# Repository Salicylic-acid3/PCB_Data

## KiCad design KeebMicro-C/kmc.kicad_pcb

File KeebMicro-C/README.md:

# KeebMicro-C

The KeebMicro-C is a Pro Micro compatible microcontroller board designed for DIY mechanical keyboards in Japan.
It is based on the same Atmel ATMega32U4 chip and can be programmed using Arduino IDE or keyboard-specific firmware such as TMK or QMK.
Conthrough, commonly used in Japan, eliminates the need for soldering.

## Links

- [fork root](https://github.com/staticintlucas/goldfish)

## Changes compared to Goldfish v2

- Conthrough support
- Reduced board outline
- Changed logo
- Added through-hole for external USB connector

## License

Released under the Creative Commons Attribution Share-Alike 4.0 License.
https://creativecommons.org/licenses/by-sa/4.0/

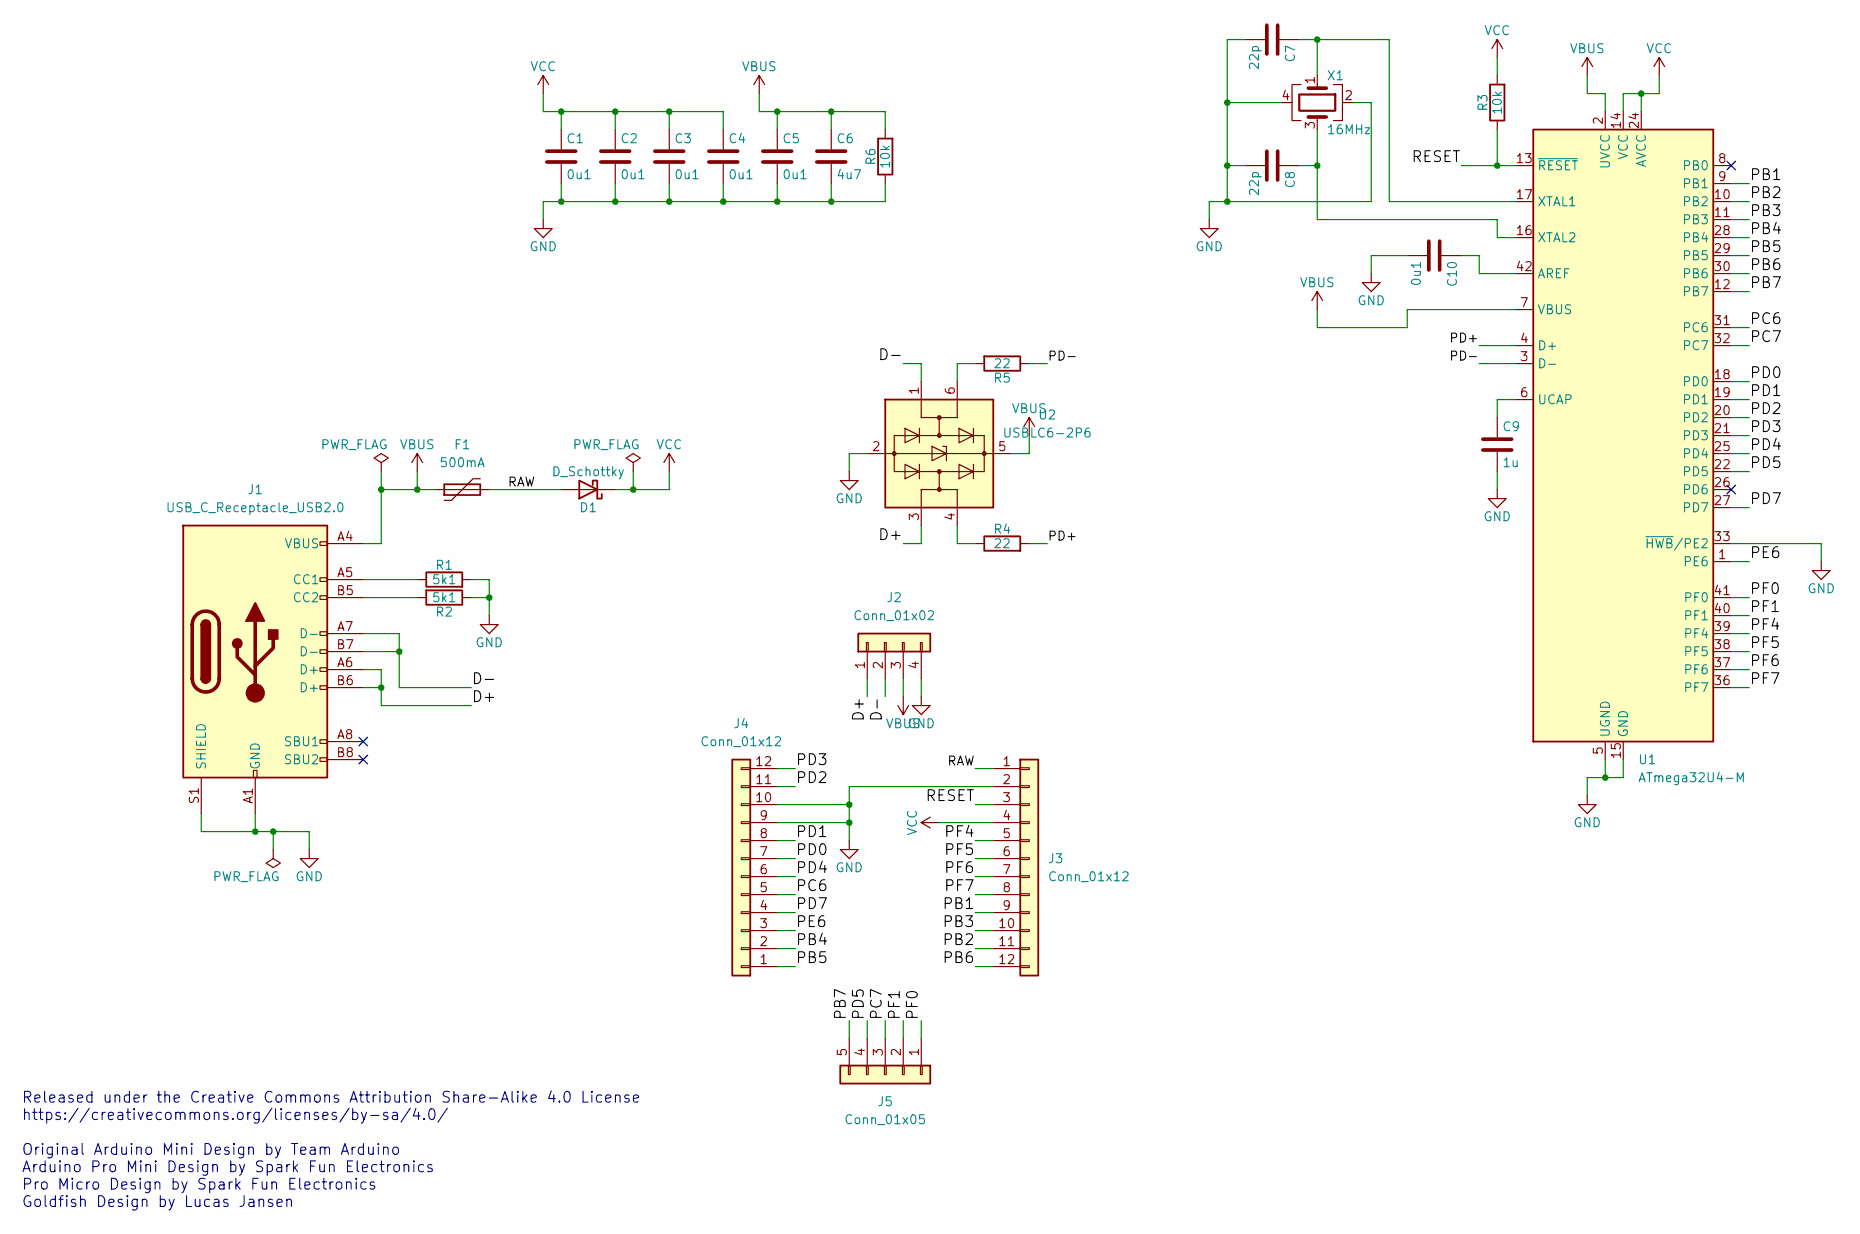
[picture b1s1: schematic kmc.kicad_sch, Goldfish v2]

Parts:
C1, C2, C3, C4, C5, C10: 0u1; C_0603_1608Metric
C6: 4u7; C_0603_1608Metric
C7, C8: 22p; C_0603_1608Metric
C9: 1u; C_0603_1608Metric
D1: D_Schottky; D_SOD-123F
F1: 500mA; Fuse_0805_2012Metric
J1: USB_C_Receptacle_USB2.0; Molex-216990_GCT-USB45xx_HRO-TYPE-C-31-M-13x
J2: Conn_01x02; Pins_USB
J3, J4: Conn_01x12; Pins_x12_Castellated
J5: Conn_01x05; Pins_x05_Castellated
R1, R2: 5k1; R_0603_1608Metric
R3, R6: 10k; R_0603_1608Metric
R4, R5: 22; R_0603_1608Metric
U1: ATmega32U4-M; QFN-44-1EP_7x7mm_P0.5mm_EP5.2x5.2mm
U2: USBLC6-2P6; SOT-666
X1: 16MHz; Crystal_SMD_SeikoEpson_FA238-4Pin_3.2x2.5mm

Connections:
/D+: J1.A6 (D+), J1.B6 (D+), J2.1, U2.3 (I/O2)
/D-: J1.A7 (D-), J1.B7 (D-), J2.2, U2.1 (I/O1)
/PB1: J3.9, U1.9 (PB1)
/PB2: J3.11, U1.10 (PB2)
/PB3: J3.10, U1.11 (PB3)
/PB4: J4.2, U1.28 (PB4)
/PB5: J4.1, U1.29 (PB5)
/PB6: J3.12, U1.30 (PB6)
/PB7: J5.5, U1.12 (PB7)
/PC6: J4.5, U1.31 (PC6)
/PC7: J5.3, U1.32 (PC7)
/PD0: J4.7, U1.18 (PD0)
/PD1: J4.8, U1.19 (PD1)
/PD2: J4.11, U1.20 (PD2)
/PD3: J4.12, U1.21 (PD3)
/PD4: J4.6, U1.25 (PD4)
/PD5: J5.4, U1.22 (PD5)
/PD7: J4.4, U1.27 (PD7)
/PD+: R4.2, U1.4 (D+)
/PD-: R5.1, U1.3 (D-)
/PE6: J4.3, U1.1 (PE6)
/PF0: J5.1, U1.41 (PF0)
/PF1: J5.2, U1.40 (PF1)
/PF4: J3.5, U1.39 (PF4)
/PF5: J3.6, U1.38 (PF5)
/PF6: J3.7, U1.37 (PF6)
/PF7: J3.8, U1.36 (PF7)
/RAW: D1.2 (A), F1.2, J3.1
/RESET: J3.3, R3.1, U1.13 (~RESET)
GND: C1.2, C2.2, C3.2, C4.2, C5.2, C6.2, C7.2, C8.2, C9.2, C10.2, J1.A1 (GND), J1.A12 (GND), J1.B1 (GND), J1.B12 (GND), J1.S1 (SHIELD), J2.4, J3.2, J4.9, J4.10, R1.2, R2.1, R6.1, U1.5 (UGND), U1.15 (GND), U1.23 (GND), U1.33 (~HWB/PE2), U1.35 (GND), U1.43 (GND), U1.45 (GND), U2.2 (GND), X1.2, X1.4
unnamed: J1.A5 (CC1), R1.1
unnamed: J1.B5 (CC2), R2.2
unnamed: R4.1, U2.4 (I/O2)
unnamed: R5.2, U2.6 (I/O1)
unnamed: C10.1, U1.42 (AREF)
unnamed: C9.1, U1.6 (UCAP)
unnamed: C7.1, U1.17 (XTAL1), X1.1
unnamed: C8.1, U1.16 (XTAL2), X1.3
VBUS: C5.1, C6.1, F1.1, J1.A4 (VBUS), J1.A9 (VBUS), J1.B4 (VBUS), J1.B9 (VBUS), J2.3, R6.2, U1.2 (UVCC), U1.7 (VBUS), U2.5 (VBUS)
VCC: C1.1, C2.1, C3.1, C4.1, D1.1 (K), J3.4, R3.2, U1.14 (VCC), U1.24 (AVCC), U1.34 (VCC), U1.44 (AVCC)

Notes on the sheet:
Released under the Creative Commons Attribution Share-Alike 4.0 License https://creativecommons.org/licenses/by-sa/4.0/ Original Arduino Mini Design by Team Arduino Arduino Pro Mini Design by Spark Fun Electronics Pro Micro Design by Spark Fun Electronics Goldfish Design by Lucas Jansen

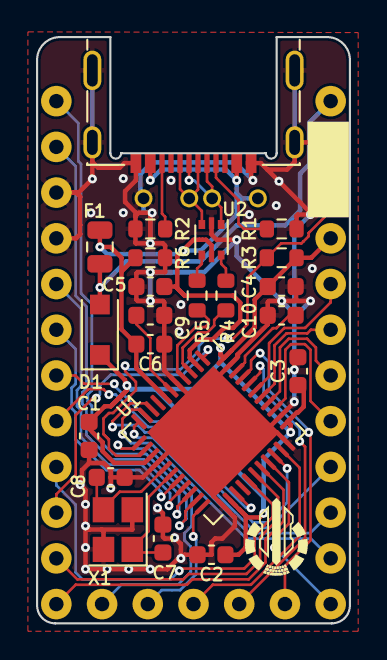
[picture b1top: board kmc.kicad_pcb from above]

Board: 2 copper layers, 17.4 x 32.6 mm, 26 parts (0 on the bottom side), 40 nets.

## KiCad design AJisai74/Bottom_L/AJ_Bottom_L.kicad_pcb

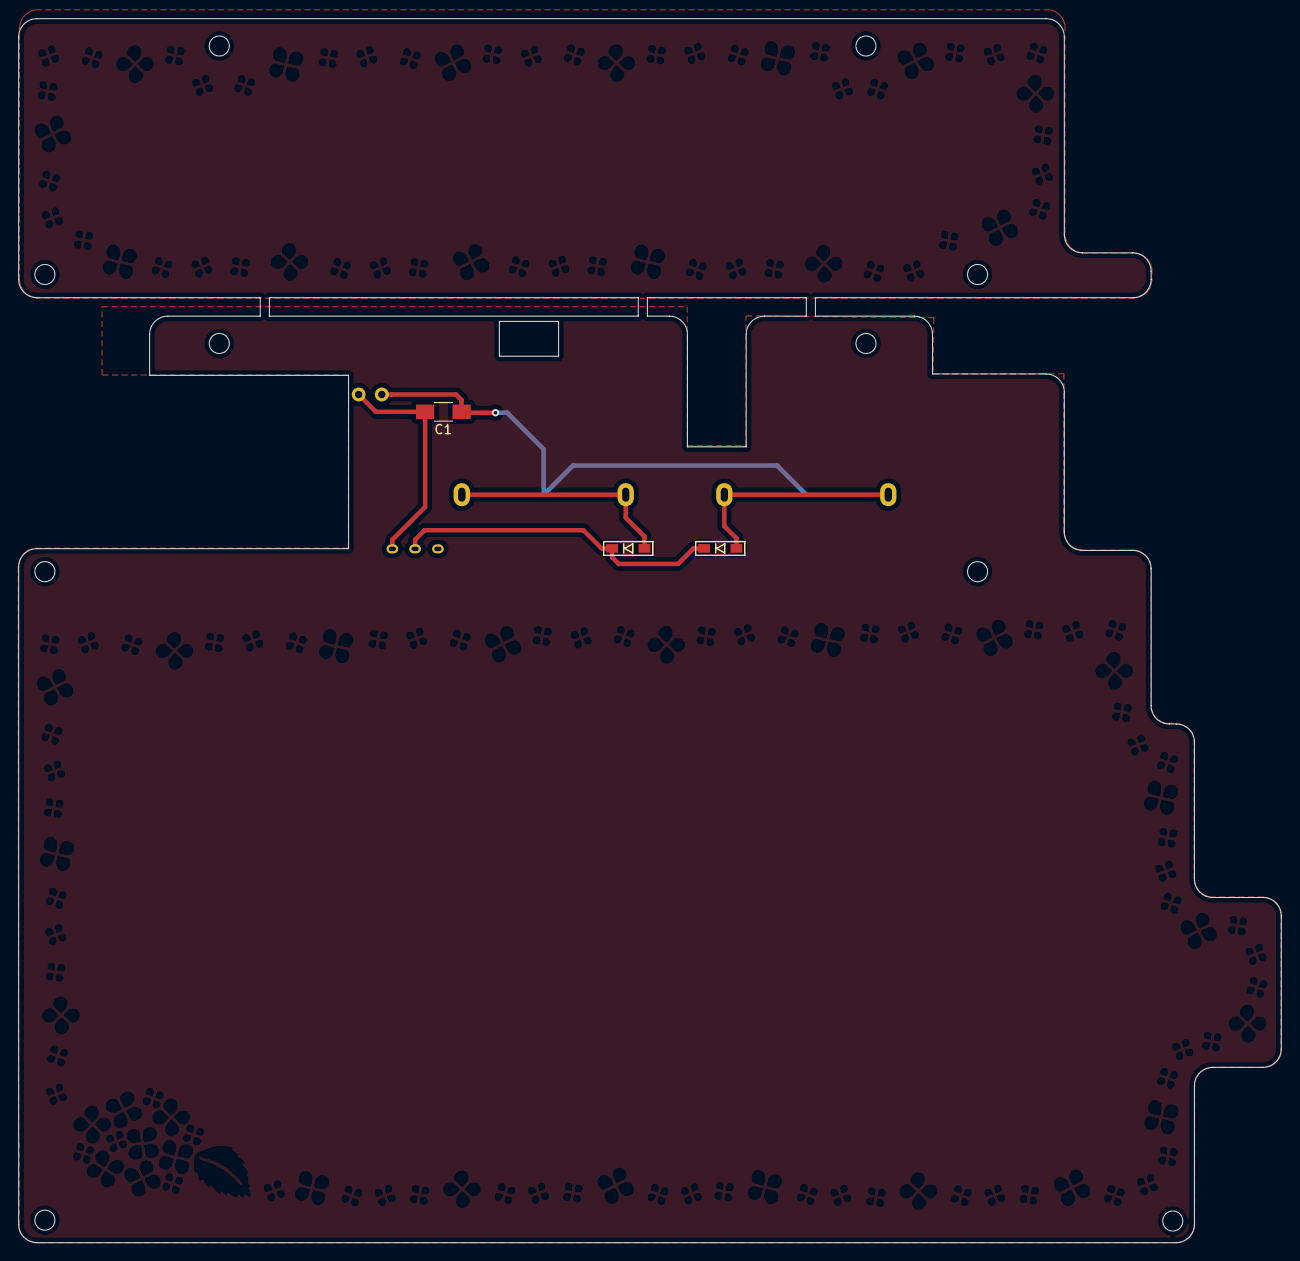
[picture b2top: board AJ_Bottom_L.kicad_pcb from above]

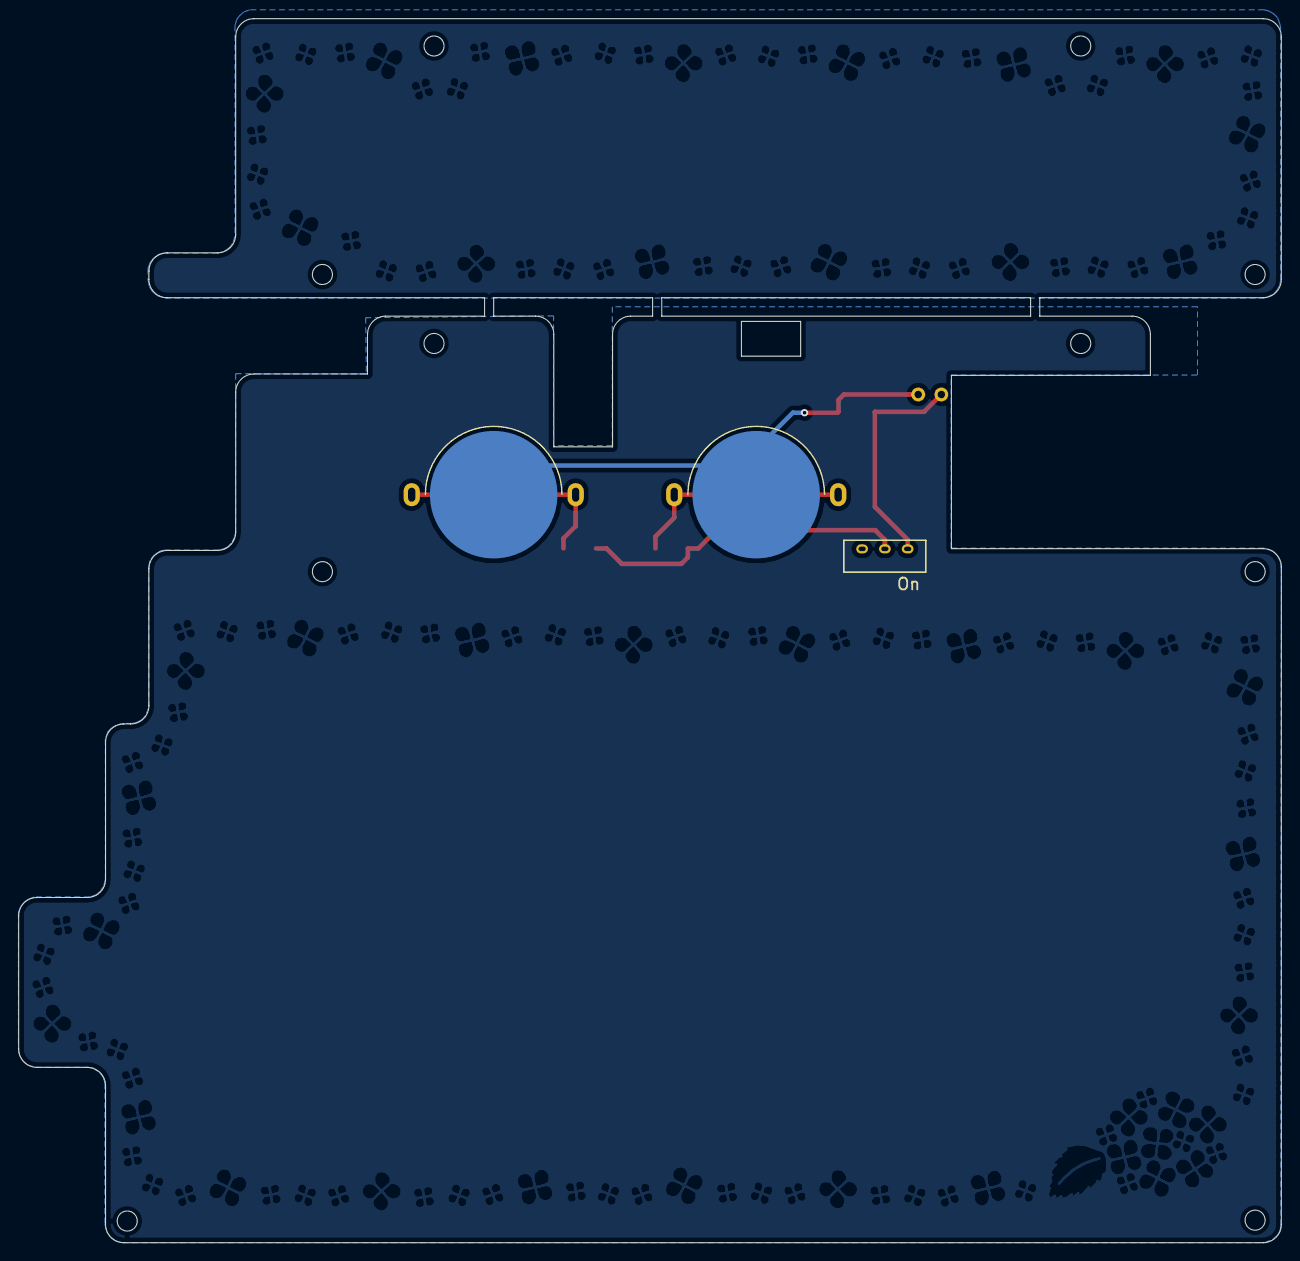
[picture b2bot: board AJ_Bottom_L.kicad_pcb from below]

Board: 2 copper layers, 138.6 x 134.4 mm, 17 parts (6 on the bottom side), 5 nets.

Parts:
BT1, BT2: Battery_Cell; ali_CR1632
C1: C_Small; C_1206_HandSoldering_Back
D1, D2: D; D3_SMD_L1
J1: Conn_01x02; 2pinBLE
J2, J2#2, J3, J3#2, J8, J9, J9#2, J10, J11, J11#2: Conn_01x01; HOLE_m2
SW1: SW_Push_SPDT; MSK-12D19

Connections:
Bat+: C1.1, J1.1, SW1.1
GND: BT1.2, BT2.2, C1.2, J1.2
unnamed: BT1.1, D1.2
unnamed: BT2.1, D2.2
unnamed: D1.1, D2.1, SW1.2

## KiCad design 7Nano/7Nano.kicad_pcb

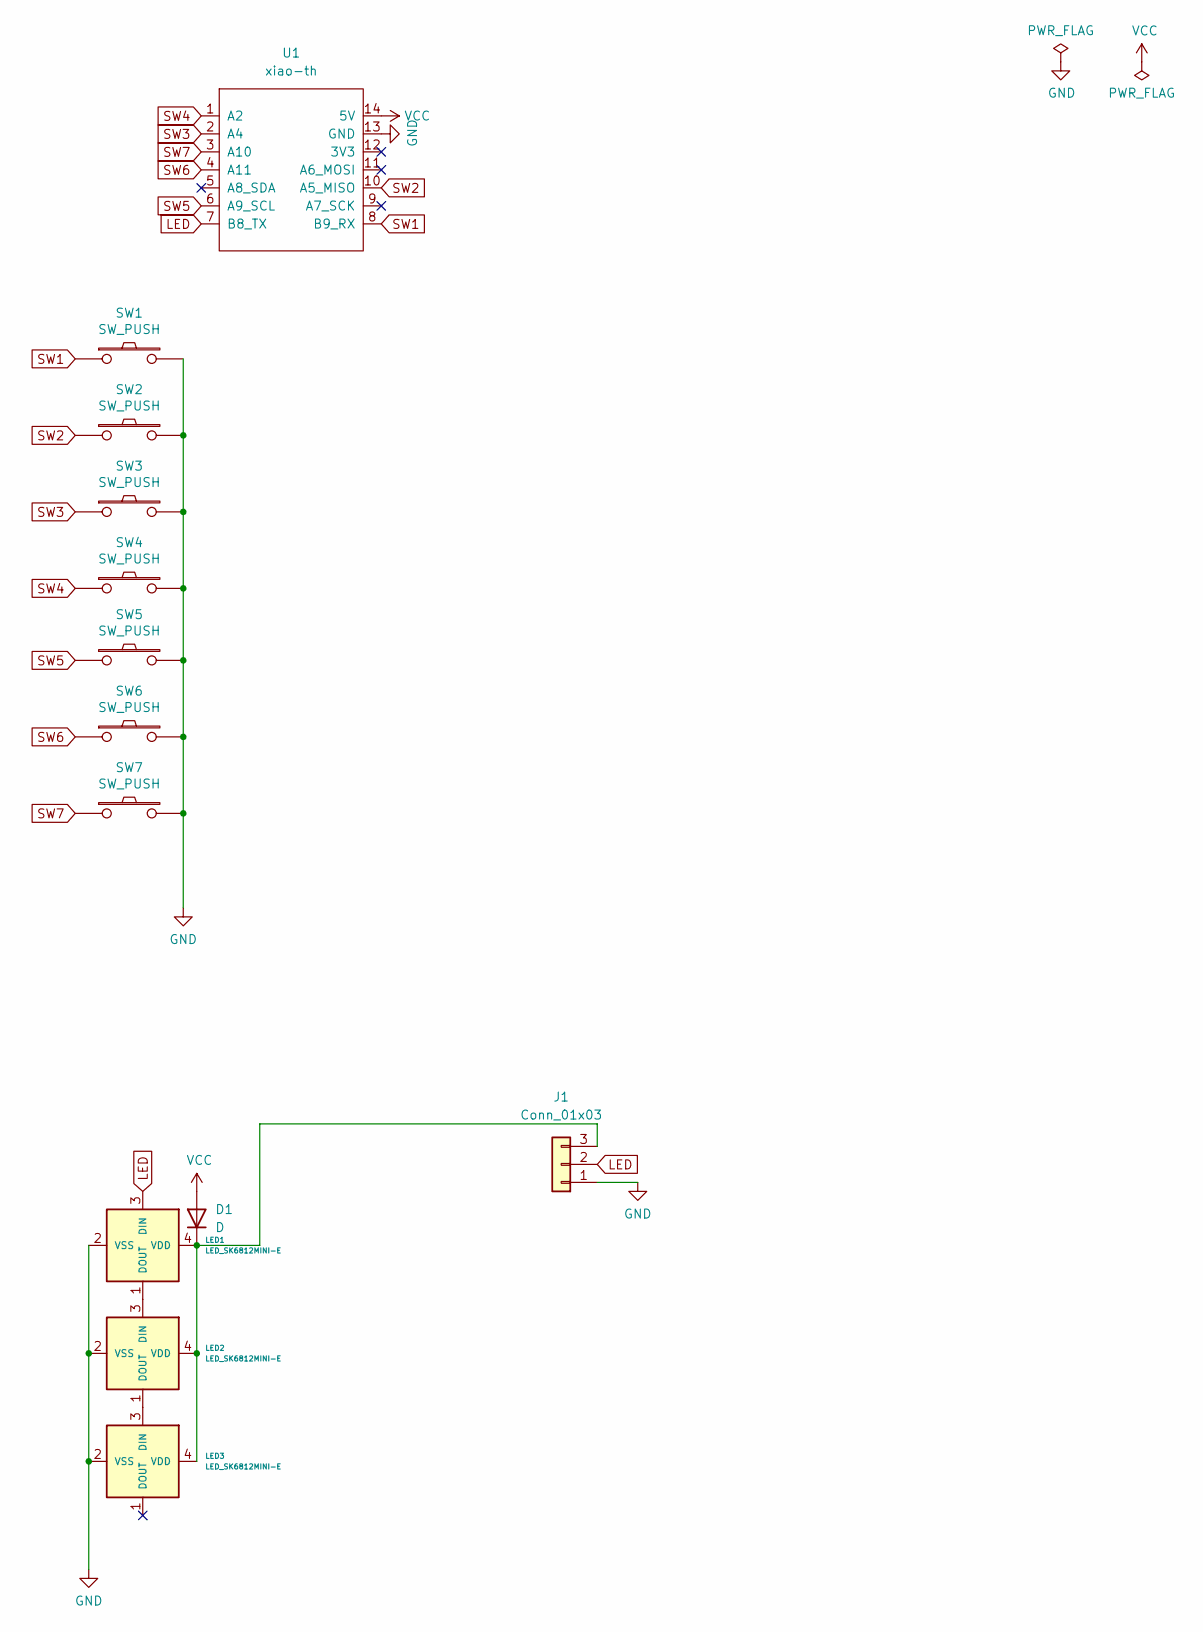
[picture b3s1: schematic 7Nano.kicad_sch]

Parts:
D1: D; Diode_SMD
J1: Conn_01x03; LED_Tape
LED1, LED2, LED3: LED_SK6812MINI-E; LED_SK6812MINI-E_BL
SW1: SW_PUSH; CherryMX_Hotswap_1u_Small1
SW2, SW3, SW7: SW_PUSH; CherryMX_Hotswap_1u
SW4, SW5: SW_PUSH; CherryMX_Hotswap_1.25u
SW6: SW_PUSH; CherryMX_Hotswap_2u_Rev
U1: xiao-th; Micon_XIAO_TH

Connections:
GND: J1.1, LED1.2 (VSS), LED2.2 (VSS), LED3.2 (VSS), SW1.2, SW2.2, SW3.2, SW4.2, SW5.2, SW6.2, SW7.2, U1.13 (GND)
LED: J1.2, LED1.3 (DIN), U1.7 (B8_TX)
unnamed: D1.1 (K), J1.3, LED1.4 (VDD), LED2.4 (VDD), LED3.4 (VDD)
unnamed: LED1.1 (DOUT), LED2.3 (DIN)
unnamed: LED2.1 (DOUT), LED3.3 (DIN)
SW1: SW1.1, U1.8 (B9_RX)
SW2: SW2.1, U1.10 (A5_MISO)
SW3: SW3.1, U1.2 (A4)
SW4: SW4.1, U1.1 (A2)
SW5: SW5.1, U1.6 (A9_SCL)
SW6: SW6.1, U1.4 (A11)
SW7: SW7.1, U1.3 (A10)
VCC: D1.2 (A), U1.14 (5V)

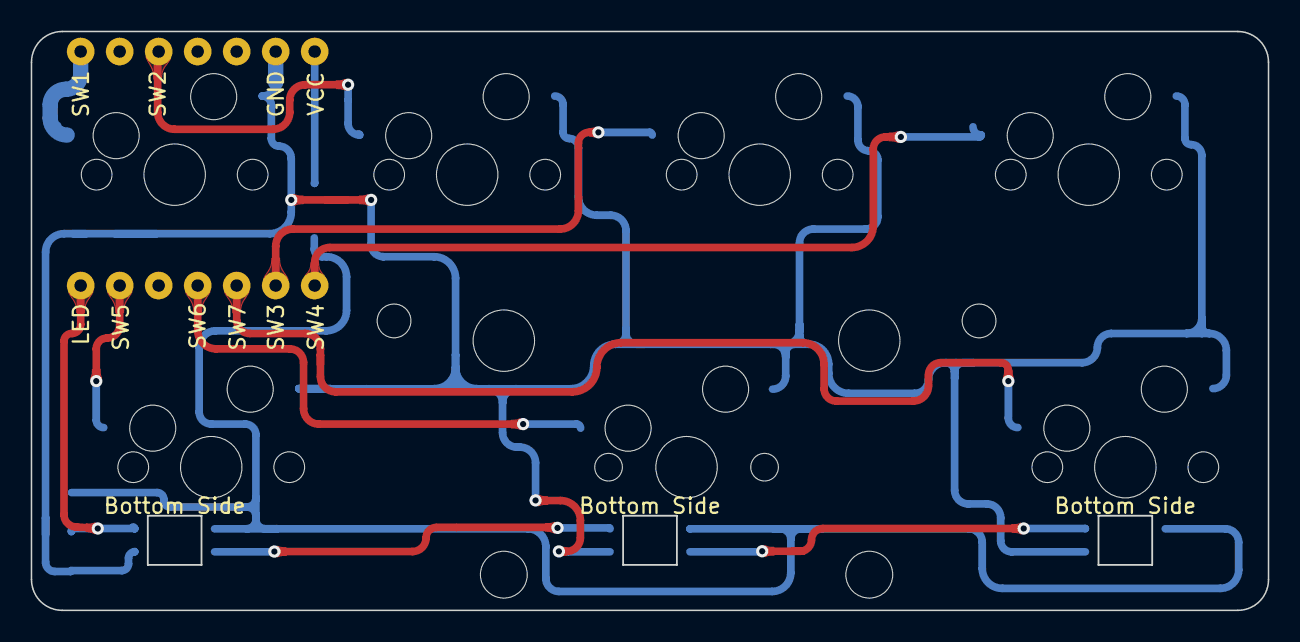
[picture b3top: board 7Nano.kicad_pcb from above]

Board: 2 copper layers, 80.6 x 37.7 mm, 15 parts (1 on the bottom side), 13 nets.

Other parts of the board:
Ref**: Val**; m2_Screw_Hole
Ref**#2: Val**; m2_Screw_Hole

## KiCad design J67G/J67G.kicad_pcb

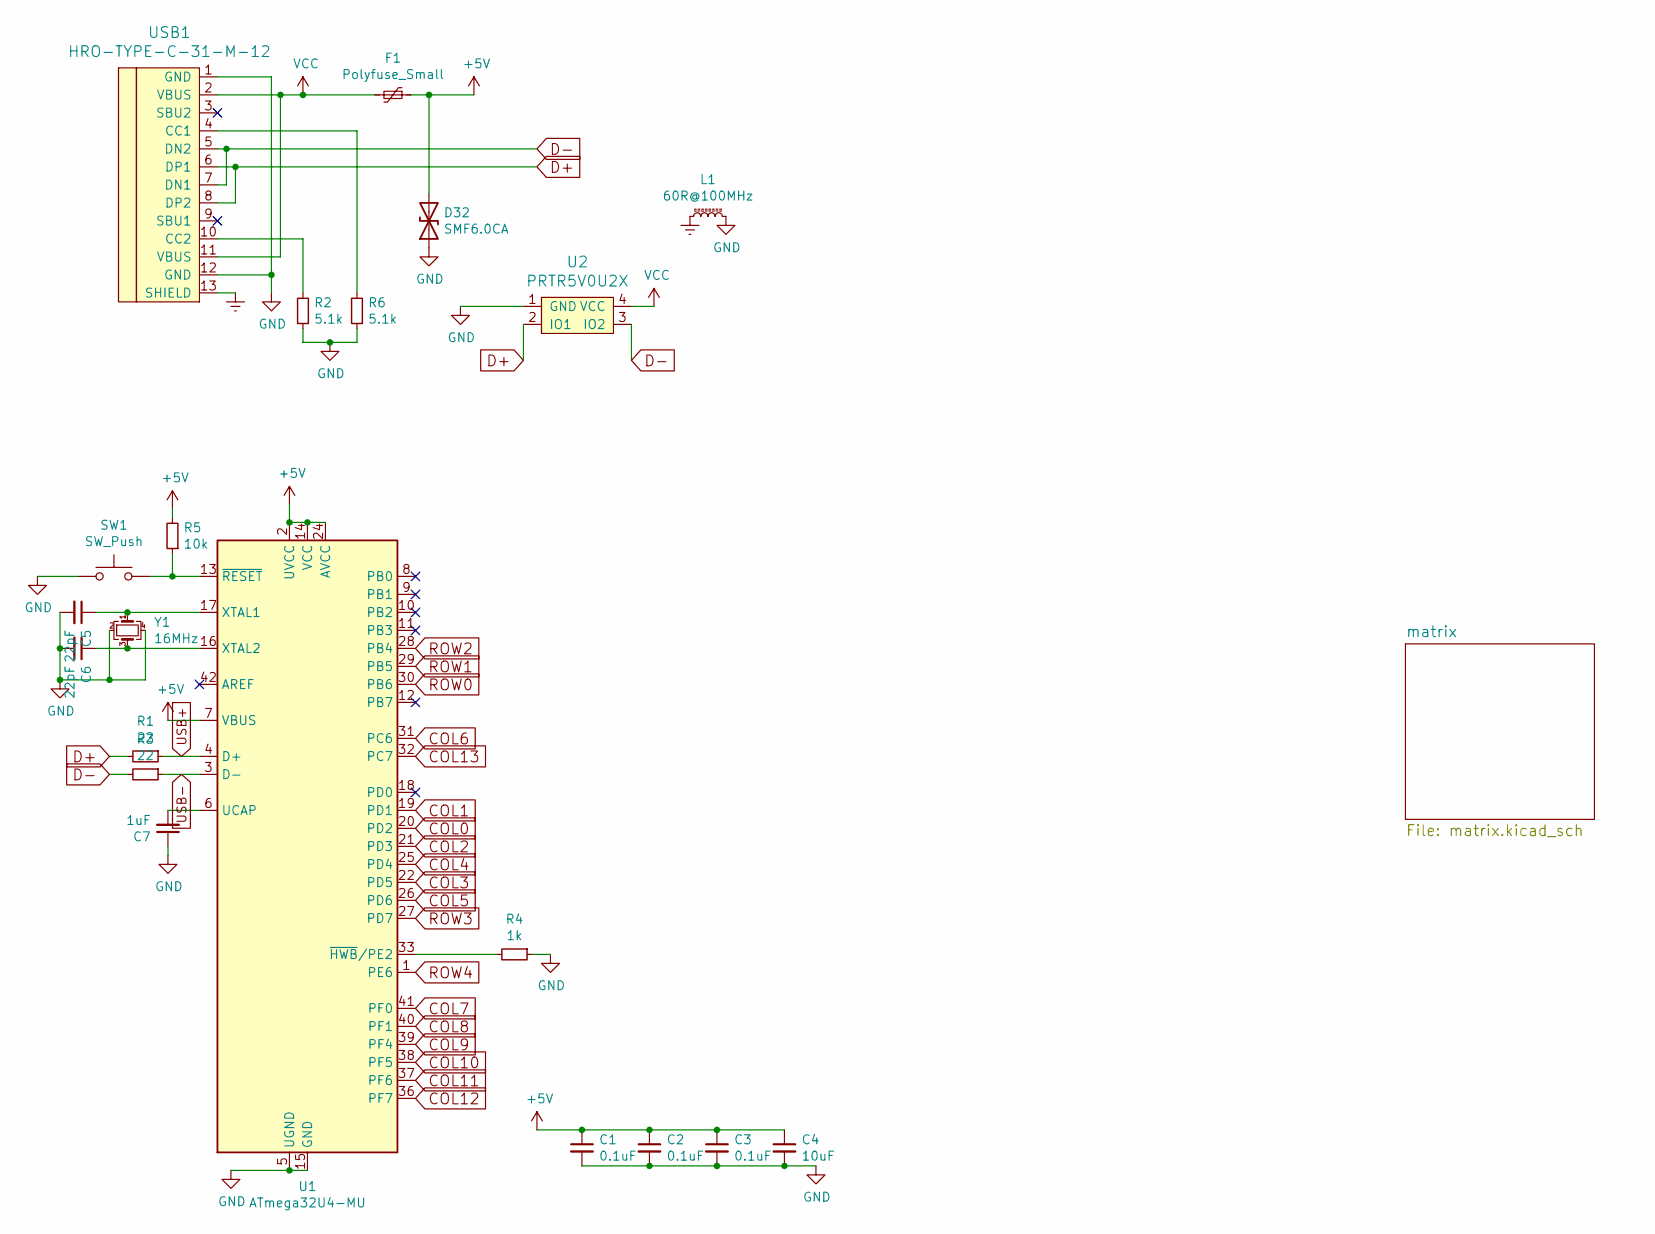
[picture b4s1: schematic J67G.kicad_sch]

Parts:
C1, C2, C3: 0.1uF; C_0603_1608Metric
C4: 10uF; C_0603_1608Metric
C5, C6: 22pF; C_0603_1608Metric
C7: 1uF; C_0603_1608Metric
D32: SMF6.0CA; D_SOD-123
F1: Polyfuse_Small; Fuse_1206_3216Metric
L1: 60R@100MHz; L_1206_3216Metric
R1, R3: 22; R_0603_1608Metric
R2, R6: 5.1k; R_0603_1608Metric
R4: 1k; R_0603_1608Metric
R5: 10k; R_0603_1608Metric
SW1: SW_Push; SW_SPST_TL3342
U1: ATmega32U4-MU; QFN-44-1EP_7x7mm_P0.5mm_EP5.2x5.2mm
U2: PRTR5V0U2X; SOT143B
USB1: HRO-TYPE-C-31-M-12; HRO-TYPE-C-31-M-12-Assembly
Y1: 16MHz; Crystal_SMD_3225-4Pin_3.2x2.5mm

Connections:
+5V: C1.1, C2.1, C3.1, C4.1, D32.2 (A2), F1.1, R5.2, U1.2 (UVCC), U1.7 (VBUS), U1.14 (VCC), U1.24 (AVCC), U1.34 (VCC), U1.44 (AVCC)
COL0: U1.20 (PD2); also elsewhere on the board
COL1: U1.19 (PD1); also elsewhere on the board
COL2: U1.21 (PD3); also elsewhere on the board
COL3: U1.22 (PD5); also elsewhere on the board
COL4: U1.25 (PD4); also elsewhere on the board
COL5: U1.26 (PD6); also elsewhere on the board
COL6: U1.31 (PC6); also elsewhere on the board
COL7: U1.41 (PF0); also elsewhere on the board
COL8: U1.40 (PF1); also elsewhere on the board
COL9: U1.39 (PF4); also elsewhere on the board
COL10: U1.38 (PF5); also elsewhere on the board
COL11: U1.37 (PF6); also elsewhere on the board
COL12: U1.36 (PF7); also elsewhere on the board
COL13: U1.32 (PC7); also elsewhere on the board
D+: R1.2, U2.2 (IO1), USB1.6 (DP1), USB1.8 (DP2)
D-: R3.2, U2.3 (IO2), USB1.5 (DN2), USB1.7 (DN1)
Earth: L1.1, USB1.13 (SHIELD)
GND: C1.2, C2.2, C3.2, C4.2, C5.2, C6.2, C7.1, D32.1 (A1), L1.2, R2.1, R4.1, R6.1, SW1.1, U1.5 (UGND), U1.15 (GND), U1.23 (GND), U1.35 (GND), U1.43 (GND), U1.45 (GND), U2.1 (GND), USB1.1 (GND), USB1.12 (GND), Y1.2, Y1.4
unnamed: C7.2, U1.6 (UCAP)
unnamed: C5.1, U1.17 (XTAL1), Y1.1
unnamed: C6.1, U1.16 (XTAL2), Y1.3
unnamed: R4.2, U1.33 (~HWB/PE2)
unnamed: R5.1, SW1.2, U1.13 (~RESET)
unnamed: R6.2, USB1.4 (CC1)
unnamed: R2.2, USB1.10 (CC2)
ROW0: U1.30 (PB6); also elsewhere on the board
ROW1: U1.29 (PB5); also elsewhere on the board
ROW2: U1.28 (PB4); also elsewhere on the board
ROW3: U1.27 (PD7); also elsewhere on the board
ROW4: U1.1 (PE6); also elsewhere on the board
USB+: R1.1, U1.4 (D+)
USB-: R3.1, U1.3 (D-)
VCC: F1.2, U2.4 (VCC), USB1.2 (VBUS), USB1.11 (VBUS)

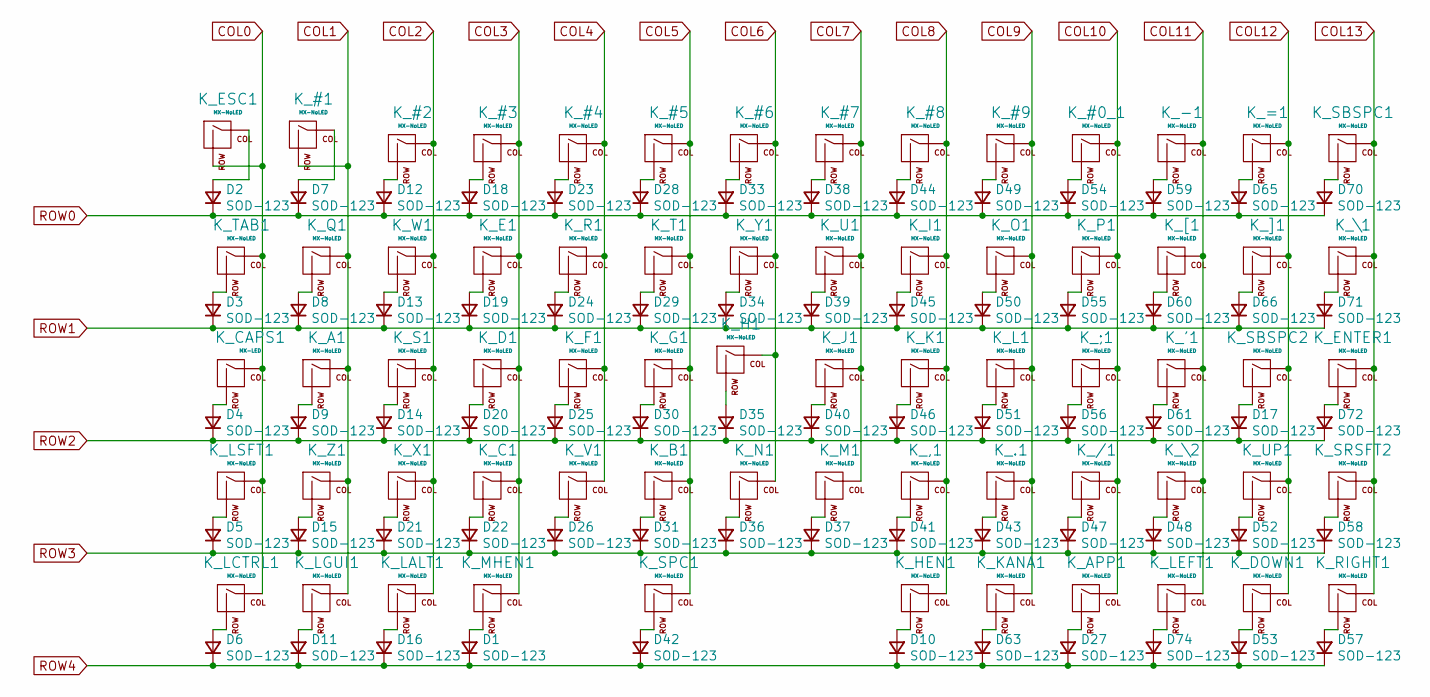
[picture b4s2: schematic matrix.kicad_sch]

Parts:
D1, D2, D3, D4, D5, D6, D7, D8, D9, D10, D11, D12, D13, D14, D15, D16, D17, D18, D19, D20, D21, D22, D23, D24, D25, D26, D27, D28, D29, D30, D31, D33, D34, D35, D36, D37, D38, D39, D40, D41, D42, D43, D44, D45, D46, D47, D48, D49, D50, D51, D52, D53, D54, D55, D56, D57, D58, D59, D60, D61, D63, D65, D66, D70, D71, D72, D74: SOD-123; D_SOD-123
K_#0_1, K_#1, K_#2, K_#3, K_#4, K_#5, K_#6, K_#7, K_#8, K_#9: MX-NoLED; CherryMX_Hotswap_1u
K_'1: MX-NoLED; CherryMX_Hotswap_1u
K_,1: MX-NoLED; CherryMX_Hotswap_1u
K_-1: MX-NoLED; CherryMX_Hotswap_1u
K_.1: MX-NoLED; CherryMX_Hotswap_1u
K_/1: MX-NoLED; CherryMX_Hotswap_1u
K_;1: MX-NoLED; CherryMX_Hotswap_1u
K_=1: MX-NoLED; CherryMX_Hotswap_1u
K_A1: MX-NoLED; CherryMX_Hotswap_1u
K_APP1: MX-NoLED; CherryMX_Hotswap_1u
K_B1: MX-NoLED; CherryMX_Hotswap_1u
K_C1: MX-NoLED; CherryMX_Hotswap_1u
K_CAPS1: MX-LED; CherryMX_Hotswap_1.75u
K_D1: MX-NoLED; CherryMX_Hotswap_1u
K_DOWN1: MX-NoLED; CherryMX_Hotswap_1u
K_E1: MX-NoLED; CherryMX_Hotswap_1u
K_ENTER1: MX-NoLED; CherryMX_Hotswap_ISO
K_ESC1: MX-NoLED; CherryMX_Hotswap_1u
K_F1: MX-NoLED; CherryMX_Hotswap_1u
K_G1: MX-NoLED; CherryMX_Hotswap_1u
K_H1: MX-NoLED; CherryMX_Hotswap_1u
K_HEN1: MX-NoLED; CherryMX_Hotswap_1.5u
K_I1: MX-NoLED; CherryMX_Hotswap_1u
K_J1: MX-NoLED; CherryMX_Hotswap_1u
K_K1: MX-NoLED; CherryMX_Hotswap_1u
K_KANA1: MX-NoLED; CherryMX_Hotswap_1.25u
K_L1: MX-NoLED; CherryMX_Hotswap_1u
K_LALT1: MX-NoLED; CherryMX_Hotswap_1.25u
K_LCTRL1: MX-NoLED; CherryMX_Hotswap_1.25u
K_LEFT1: MX-NoLED; CherryMX_Hotswap_1u
K_LGUI1: MX-NoLED; CherryMX_Hotswap_1.25u
K_LSFT1: MX-NoLED; CherryMX_Hotswap_2u
K_M1: MX-NoLED; CherryMX_Hotswap_1u
K_MHEN1: MX-NoLED; CherryMX_Hotswap_1.5u
K_N1: MX-NoLED; CherryMX_Hotswap_1u
K_O1: MX-NoLED; CherryMX_Hotswap_1u
K_P1: MX-NoLED; CherryMX_Hotswap_1u
K_Q1: MX-NoLED; CherryMX_Hotswap_1u
K_R1: MX-NoLED; CherryMX_Hotswap_1u
K_RIGHT1: MX-NoLED; CherryMX_Hotswap_1u
K_S1: MX-NoLED; CherryMX_Hotswap_1u
K_SBSPC1, K_SBSPC2: MX-NoLED; CherryMX_Hotswap_1u
K_SPC1: MX-NoLED; CherryMX_Hotswap_3u_Rev
K_SRSFT2: MX-NoLED; CherryMX_Hotswap_1u
K_T1: MX-NoLED; CherryMX_Hotswap_1u
K_TAB1: MX-NoLED; CherryMX_Hotswap_1.5u
K_U1: MX-NoLED; CherryMX_Hotswap_1u
K_UP1: MX-NoLED; CherryMX_Hotswap_1u
K_V1: MX-NoLED; CherryMX_Hotswap_1u
K_W1: MX-NoLED; CherryMX_Hotswap_1u
K_X1: MX-NoLED; CherryMX_Hotswap_1u
K_Y1: MX-NoLED; CherryMX_Hotswap_1u
K_Z1: MX-NoLED; CherryMX_Hotswap_1u
K_[1: MX-NoLED; CherryMX_Hotswap_1u
K_\1, K_\2: MX-NoLED; CherryMX_Hotswap_1u
K_]1: MX-NoLED; CherryMX_Hotswap_1u

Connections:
COL0: K_CAPS1.1 (COL), K_ESC1.2 (ROW), K_LCTRL1.1 (COL), K_LSFT1.1 (COL), K_TAB1.1 (COL); also elsewhere on the board
COL1: K_#1.2 (ROW), K_A1.1 (COL), K_LGUI1.1 (COL), K_Q1.1 (COL), K_Z1.1 (COL); also elsewhere on the board
COL2: K_#2.1 (COL), K_LALT1.1 (COL), K_S1.1 (COL), K_W1.1 (COL), K_X1.1 (COL); also elsewhere on the board
COL3: K_#3.1 (COL), K_C1.1 (COL), K_D1.1 (COL), K_E1.1 (COL), K_MHEN1.1 (COL); also elsewhere on the board
COL4: K_#4.1 (COL), K_F1.1 (COL), K_R1.1 (COL), K_V1.1 (COL); also elsewhere on the board
COL5: K_#5.1 (COL), K_B1.1 (COL), K_G1.1 (COL), K_SPC1.1 (COL), K_T1.1 (COL); also elsewhere on the board
COL6: K_#6.1 (COL), K_H1.1 (COL), K_N1.1 (COL), K_Y1.1 (COL); also elsewhere on the board
COL7: K_#7.1 (COL), K_J1.1 (COL), K_M1.1 (COL), K_U1.1 (COL); also elsewhere on the board
COL8: K_#8.1 (COL), K_,1.1 (COL), K_HEN1.1 (COL), K_I1.1 (COL), K_K1.1 (COL); also elsewhere on the board
COL9: K_#9.1 (COL), K_.1.1 (COL), K_KANA1.1 (COL), K_L1.1 (COL), K_O1.1 (COL); also elsewhere on the board
COL10: K_#0_1.1 (COL), K_/1.1 (COL), K_;1.1 (COL), K_APP1.1 (COL), K_P1.1 (COL); also elsewhere on the board
COL11: K_'1.1 (COL), K_-1.1 (COL), K_LEFT1.1 (COL), K_[1.1 (COL), K_\2.1 (COL); also elsewhere on the board
COL12: K_=1.1 (COL), K_DOWN1.1 (COL), K_SBSPC2.1 (COL), K_UP1.1 (COL), K_]1.1 (COL); also elsewhere on the board
COL13: K_ENTER1.1 (COL), K_RIGHT1.1 (COL), K_SBSPC1.1 (COL), K_SRSFT2.1 (COL), K_\1.1 (COL); also elsewhere on the board
unnamed: D1.2 (A), K_MHEN1.2 (ROW)
unnamed: D2.2 (A), K_ESC1.1 (COL)
unnamed: D3.2 (A), K_TAB1.2 (ROW)
unnamed: D4.2 (A), K_CAPS1.2 (ROW)
unnamed: D5.2 (A), K_LSFT1.2 (ROW)
unnamed: D6.2 (A), K_LCTRL1.2 (ROW)
unnamed: D7.2 (A), K_#1.1 (COL)
unnamed: D8.2 (A), K_Q1.2 (ROW)
unnamed: D9.2 (A), K_A1.2 (ROW)
unnamed: D10.2 (A), K_HEN1.2 (ROW)
unnamed: D11.2 (A), K_LGUI1.2 (ROW)
unnamed: D12.2 (A), K_#2.2 (ROW)
unnamed: D13.2 (A), K_W1.2 (ROW)
unnamed: D14.2 (A), K_S1.2 (ROW)
unnamed: D15.2 (A), K_Z1.2 (ROW)
unnamed: D16.2 (A), K_LALT1.2 (ROW)
unnamed: D17.2 (A), K_SBSPC2.2 (ROW)
unnamed: D18.2 (A), K_#3.2 (ROW)
unnamed: D19.2 (A), K_E1.2 (ROW)
unnamed: D20.2 (A), K_D1.2 (ROW)
unnamed: D21.2 (A), K_X1.2 (ROW)
unnamed: D22.2 (A), K_C1.2 (ROW)
unnamed: D23.2 (A), K_#4.2 (ROW)
unnamed: D24.2 (A), K_R1.2 (ROW)
unnamed: D25.2 (A), K_F1.2 (ROW)
unnamed: D26.2 (A), K_V1.2 (ROW)
unnamed: D27.2 (A), K_APP1.2 (ROW)
unnamed: D28.2 (A), K_#5.2 (ROW)
unnamed: D29.2 (A), K_T1.2 (ROW)
unnamed: D30.2 (A), K_G1.2 (ROW)
unnamed: D31.2 (A), K_B1.2 (ROW)
unnamed: D33.2 (A), K_#6.2 (ROW)
unnamed: D34.2 (A), K_Y1.2 (ROW)
unnamed: D35.2 (A), K_H1.2 (ROW)
unnamed: D36.2 (A), K_N1.2 (ROW)
unnamed: D37.2 (A), K_M1.2 (ROW)
unnamed: D38.2 (A), K_#7.2 (ROW)
unnamed: D39.2 (A), K_U1.2 (ROW)
unnamed: D40.2 (A), K_J1.2 (ROW)
unnamed: D41.2 (A), K_,1.2 (ROW)
unnamed: D42.2 (A), K_SPC1.2 (ROW)
unnamed: D43.2 (A), K_.1.2 (ROW)
unnamed: D44.2 (A), K_#8.2 (ROW)
unnamed: D45.2 (A), K_I1.2 (ROW)
unnamed: D46.2 (A), K_K1.2 (ROW)
unnamed: D47.2 (A), K_/1.2 (ROW)
unnamed: D48.2 (A), K_\2.2 (ROW)
unnamed: D49.2 (A), K_#9.2 (ROW)
unnamed: D50.2 (A), K_O1.2 (ROW)
unnamed: D51.2 (A), K_L1.2 (ROW)
unnamed: D52.2 (A), K_UP1.2 (ROW)
unnamed: D53.2 (A), K_DOWN1.2 (ROW)
unnamed: D54.2 (A), K_#0_1.2 (ROW)
unnamed: D55.2 (A), K_P1.2 (ROW)
unnamed: D56.2 (A), K_;1.2 (ROW)
unnamed: D57.2 (A), K_RIGHT1.2 (ROW)
unnamed: D58.2 (A), K_SRSFT2.2 (ROW)
unnamed: D59.2 (A), K_-1.2 (ROW)
unnamed: D60.2 (A), K_[1.2 (ROW)
unnamed: D61.2 (A), K_'1.2 (ROW)
unnamed: D63.2 (A), K_KANA1.2 (ROW)
unnamed: D65.2 (A), K_=1.2 (ROW)
unnamed: D66.2 (A), K_]1.2 (ROW)
unnamed: D70.2 (A), K_SBSPC1.2 (ROW)
unnamed: D71.2 (A), K_\1.2 (ROW)
unnamed: D72.2 (A), K_ENTER1.2 (ROW)
unnamed: D74.2 (A), K_LEFT1.2 (ROW)
ROW0: D2.1 (K), D7.1 (K), D12.1 (K), D18.1 (K), D23.1 (K), D28.1 (K), D33.1 (K), D38.1 (K), D44.1 (K), D49.1 (K), D54.1 (K), D59.1 (K), D65.1 (K), D70.1 (K); also elsewhere on the board
ROW1: D3.1 (K), D8.1 (K), D13.1 (K), D19.1 (K), D24.1 (K), D29.1 (K), D34.1 (K), D39.1 (K), D45.1 (K), D50.1 (K), D55.1 (K), D60.1 (K), D66.1 (K), D71.1 (K); also elsewhere on the board
ROW2: D4.1 (K), D9.1 (K), D14.1 (K), D17.1 (K), D20.1 (K), D25.1 (K), D30.1 (K), D35.1 (K), D40.1 (K), D46.1 (K), D51.1 (K), D56.1 (K), D61.1 (K), D72.1 (K); also elsewhere on the board
ROW3: D5.1 (K), D15.1 (K), D21.1 (K), D22.1 (K), D26.1 (K), D31.1 (K), D36.1 (K), D37.1 (K), D41.1 (K), D43.1 (K), D47.1 (K), D48.1 (K), D52.1 (K), D58.1 (K); also elsewhere on the board
ROW4: D1.1 (K), D6.1 (K), D10.1 (K), D11.1 (K), D16.1 (K), D27.1 (K), D42.1 (K), D53.1 (K), D57.1 (K), D63.1 (K), D74.1 (K); also elsewhere on the board

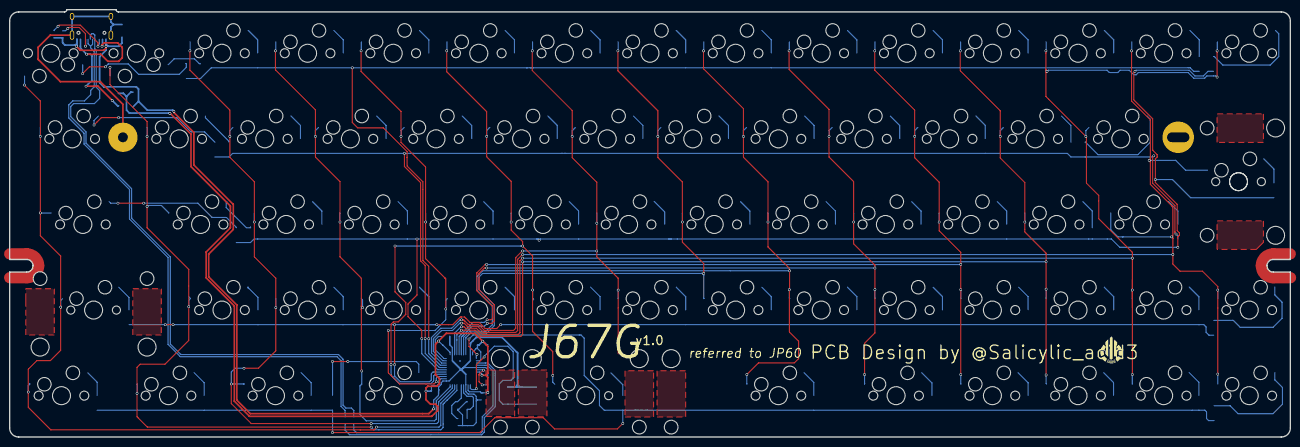
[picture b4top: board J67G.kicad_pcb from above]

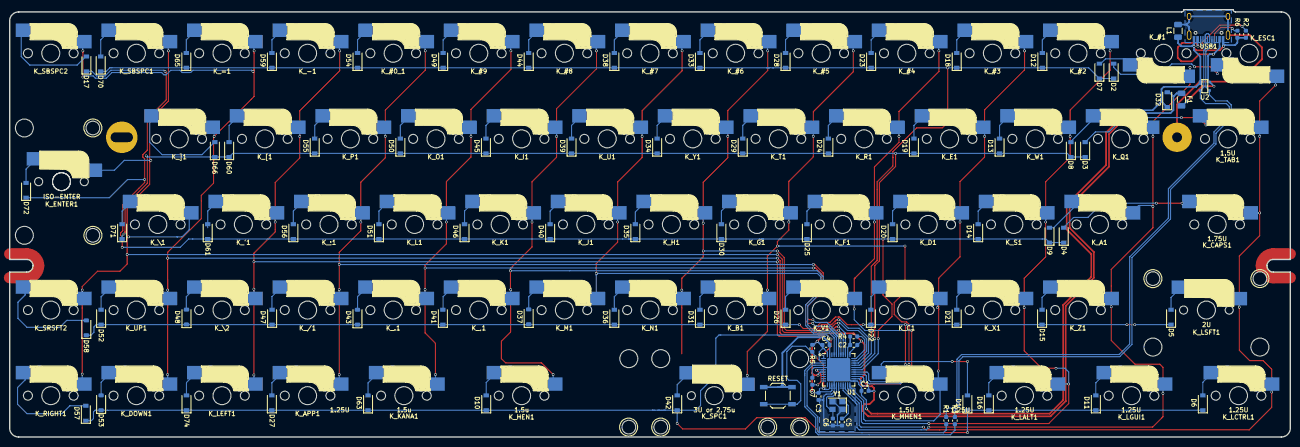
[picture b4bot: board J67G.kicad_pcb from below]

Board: 2 copper layers, 285.0 x 95.1 mm, 157 parts (88 on the bottom side), 101 nets.

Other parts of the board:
REFe: 60_Outline; 60_Outline-Modded-Extreme
SW2: KEY_SWITCH; CherryMX_Hotswap_2.75u_Rev

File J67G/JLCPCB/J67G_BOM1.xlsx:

Comment | Designator | Footprint | LCSC Part #（optional）
0.1uF | C1 C2 C3 | C_0603_1608Metric | C14663
10uF | C4 | C_0603_1608Metric | C19702
1uF | C7 | C_0603_1608Metric | C15849
22pF | C5 C6 | C_0603_1608Metric | C1653
SMF6.0CA | D32 | D_SOD-123 | C123791
SOD-123 | D1 D2 D3 D4 D5 D6 D7 D8 D9 D10 D11 D12 D13 D14 D15 D16 D17 D18 D19 D20 D21 D22 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 | D_SOD-123 | C81598
Polyfuse_Small | F1 | Fuse_1206_3216Metric | C70082
Hotswap-Socket | K_.1,K_COMMA1,K_#2,K_#3,K_#4,K_#5,K_#6,K_#7,K_#8,K_#9,K_#0_1,K_'1,K_-1,K_/1,K_;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 | CherryMX_Hotswap_1u
Hotswap-Socket | K_#1 | CherryMX_Hotswap_1u_Small8
Hotswap-Socket | K_ENTER1 | CherryMX_Hotswap_ISO
Hotswap-Socket | K_ESC1,K_Q1 | CherryMX_Hotswap_1u_Small2
Hotswap-Socket | K_LALT1,K_LCTRL1,K_KANA1,K_LGUI1 | CherryMX_Hotswap_1.25u
Hotswap-Socket | K_LSFT1 | CherryMX_Hotswap_2u
Hotswap-Socket | K_SPC1 | CherryMX_Hotswap_3u_Rev
Hotswap-Socket | K_TAB1,K_MHEN1,K_HEN1 | CherryMX_Hotswap_1.5u
Hotswap-Socket | K_CAPS1 | CherryMX_Hotswap_1.75u
60R@100MHz | L1 | L_1206_3216Metric | C33600
10k | R5 | R_0603_1608Metric | C25804
1k | R4 | R_0603_1608Metric | C21190
22 | R1 R3 | R_0603_1608Metric | C23345
5.1k | R2 R6 | R_0603_1608Metric | C23186
SW_Push | SW1 | SW_SPST_TL3342 | C318884
ATmega32U4-MU | U1 | QFN-44-1EP_7x7mm_P0.5mm_EP5.2x5.2mm | C45874
PRTR5V0U2X | U2 | SOT143B | C78442
HRO-TYPE-C-31-M-12 | USB1 | HRO-TYPE-C-31-M-12-Assembly | C165948
16MHz | Y1 | Crystal_SMD_3225-4Pin_3.2x2.5mm | C13738
